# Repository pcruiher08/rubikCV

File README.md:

# rubikCV

## Objectives

## Approach

## Development

### Mechanics
#### Brief discussion about motors
#### MoYu Weilong gts v2
#### First design (unreliable)
#### Second design (screenshots and video)
#### Screw joint design
#### Motor-Cube joints
#### 3D printing and laser cutting

### Electronics
#### Controller decision (raspberry)
#### A4988 Motor driver
#### LCD
#### 18650 lithium batteries
#### LEDs
#### Arduino with LEDs and how it would be implemented on the raspberry (level shifter)
#### Brief disccussion about the pcb and the breadboard
#### WebCam

### Software

#### OpenCV justification
* Image processing (5 pictures per face)
* Arucos (Augmented reality and geometry functions)
* HSV
* Dominant Color algorithm
#### Cube map (diagrams, polygon class)
#### States machine (scanning phase with pre defined movements)
#### Kociemba
#### Motor movement (parser, motor class, motor speed)
#### LEDs
#### LCD (LCD class)

## Results

## Improvements

## Conlusions

## DIY

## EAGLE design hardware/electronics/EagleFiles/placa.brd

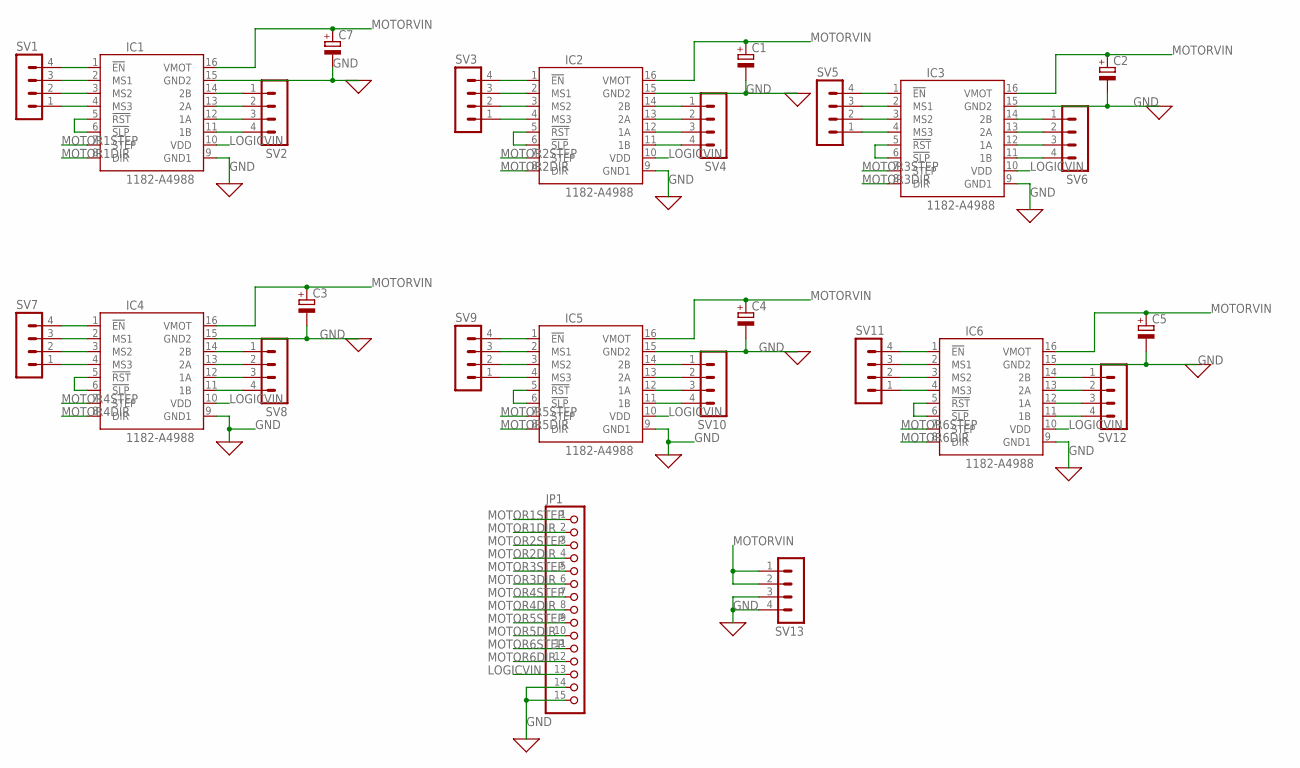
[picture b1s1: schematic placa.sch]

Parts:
C1, C2, C3, C4, C5, C7: CPOL-EUE2.5-7; E2,5-7
IC1, IC2, IC3, IC4, IC5, IC6: 1182-A4988; A4988
JP1: PINHD-1X15; 1X15
SV1, SV2, SV3, SV4, SV5, SV6, SV7, SV8, SV9, SV10, SV11, SV12, SV13: MA04-1

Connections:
GND: C1.-, C2.-, C3.-, C4.-, C5.-, C7.-, IC1.9 (GND1), IC1.15 (GND2), IC2.9 (GND1), IC2.15 (GND2), IC3.9 (GND1), IC3.15 (GND2), IC4.9 (GND1), IC4.15 (GND2), IC5.9 (GND1), IC5.15 (GND2), IC6.9 (GND1), IC6.15 (GND2), JP1.14, JP1.15, SV13.3, SV13.4
LOGICVIN: IC1.10 (VDD), IC2.10 (VDD), IC3.10 (VDD), IC4.10 (VDD), IC5.10 (VDD), IC6.10 (VDD), JP1.13
MOTOR1DIR: IC1.8 (DIR), JP1.2
MOTOR1STEP: IC1.7 (STEP), JP1.1
MOTOR2DIR: IC2.8 (DIR), JP1.4
MOTOR2STEP: IC2.7 (STEP), JP1.3
MOTOR3DIR: IC3.8 (DIR), JP1.6
MOTOR3STEP: IC3.7 (STEP), JP1.5
MOTOR4DIR: IC4.8 (DIR), JP1.8
MOTOR4STEP: IC4.7 (STEP), JP1.7
MOTOR5DIR: IC5.8 (DIR), JP1.10
MOTOR5STEP: IC5.7 (STEP), JP1.9
MOTOR6DIR: IC6.8 (DIR), JP1.12
MOTOR6STEP: IC6.7 (STEP), JP1.11
MOTORVIN: C1.+, C2.+, C3.+, C4.+, C5.+, C7.+, IC1.16 (VMOT), IC2.16 (VMOT), IC3.16 (VMOT), IC4.16 (VMOT), IC5.16 (VMOT), IC6.16 (VMOT), SV13.1, SV13.2
unnamed: IC1.1 (!EN), SV1.4
unnamed: IC1.2 (MS1), SV1.3
unnamed: IC1.3 (MS2), SV1.2
unnamed: IC1.4 (MS3), SV1.1
unnamed: IC1.5 (!RST), IC1.6 (!SLP)
unnamed: IC2.1 (!EN), SV3.4
unnamed: IC2.2 (MS1), SV3.3
unnamed: IC2.3 (MS2), SV3.2
unnamed: IC1.14 (2B), SV2.1
unnamed: IC1.13 (2A), SV2.2
unnamed: IC1.12 (1A), SV2.3
unnamed: IC1.11 (1B), SV2.4
unnamed: IC2.4 (MS3), SV3.1
unnamed: IC2.5 (!RST), IC2.6 (!SLP)
unnamed: IC2.14 (2B), SV4.1
unnamed: IC2.13 (2A), SV4.2
unnamed: IC2.12 (1A), SV4.3
unnamed: IC2.11 (1B), SV4.4
unnamed: IC3.1 (!EN), SV5.4
unnamed: IC3.2 (MS1), SV5.3
unnamed: IC3.3 (MS2), SV5.2
unnamed: IC3.4 (MS3), SV5.1
unnamed: IC3.5 (!RST), IC3.6 (!SLP)
unnamed: IC3.14 (2B), SV6.1
unnamed: IC3.13 (2A), SV6.2
unnamed: IC3.12 (1A), SV6.3
unnamed: IC3.11 (1B), SV6.4
unnamed: IC4.1 (!EN), SV7.4
unnamed: IC4.2 (MS1), SV7.3
unnamed: IC4.3 (MS2), SV7.2
unnamed: IC4.4 (MS3), SV7.1
unnamed: IC4.5 (!RST), IC4.6 (!SLP)
unnamed: IC4.14 (2B), SV8.1
unnamed: IC4.13 (2A), SV8.2
unnamed: IC4.12 (1A), SV8.3
unnamed: IC4.11 (1B), SV8.4
unnamed: IC5.1 (!EN), SV9.4
unnamed: IC5.2 (MS1), SV9.3
unnamed: IC5.3 (MS2), SV9.2
unnamed: IC5.4 (MS3), SV9.1
unnamed: IC5.5 (!RST), IC5.6 (!SLP)
unnamed: IC5.14 (2B), SV10.1
unnamed: IC5.13 (2A), SV10.2
unnamed: IC5.12 (1A), SV10.3
unnamed: IC5.11 (1B), SV10.4
unnamed: IC6.1 (!EN), SV11.4
unnamed: IC6.2 (MS1), SV11.3
unnamed: IC6.3 (MS2), SV11.2
unnamed: IC6.4 (MS3), SV11.1
unnamed: IC6.5 (!RST), IC6.6 (!SLP)
unnamed: IC6.14 (2B), SV12.1
unnamed: IC6.13 (2A), SV12.2
unnamed: IC6.12 (1A), SV12.3
unnamed: IC6.11 (1B), SV12.4

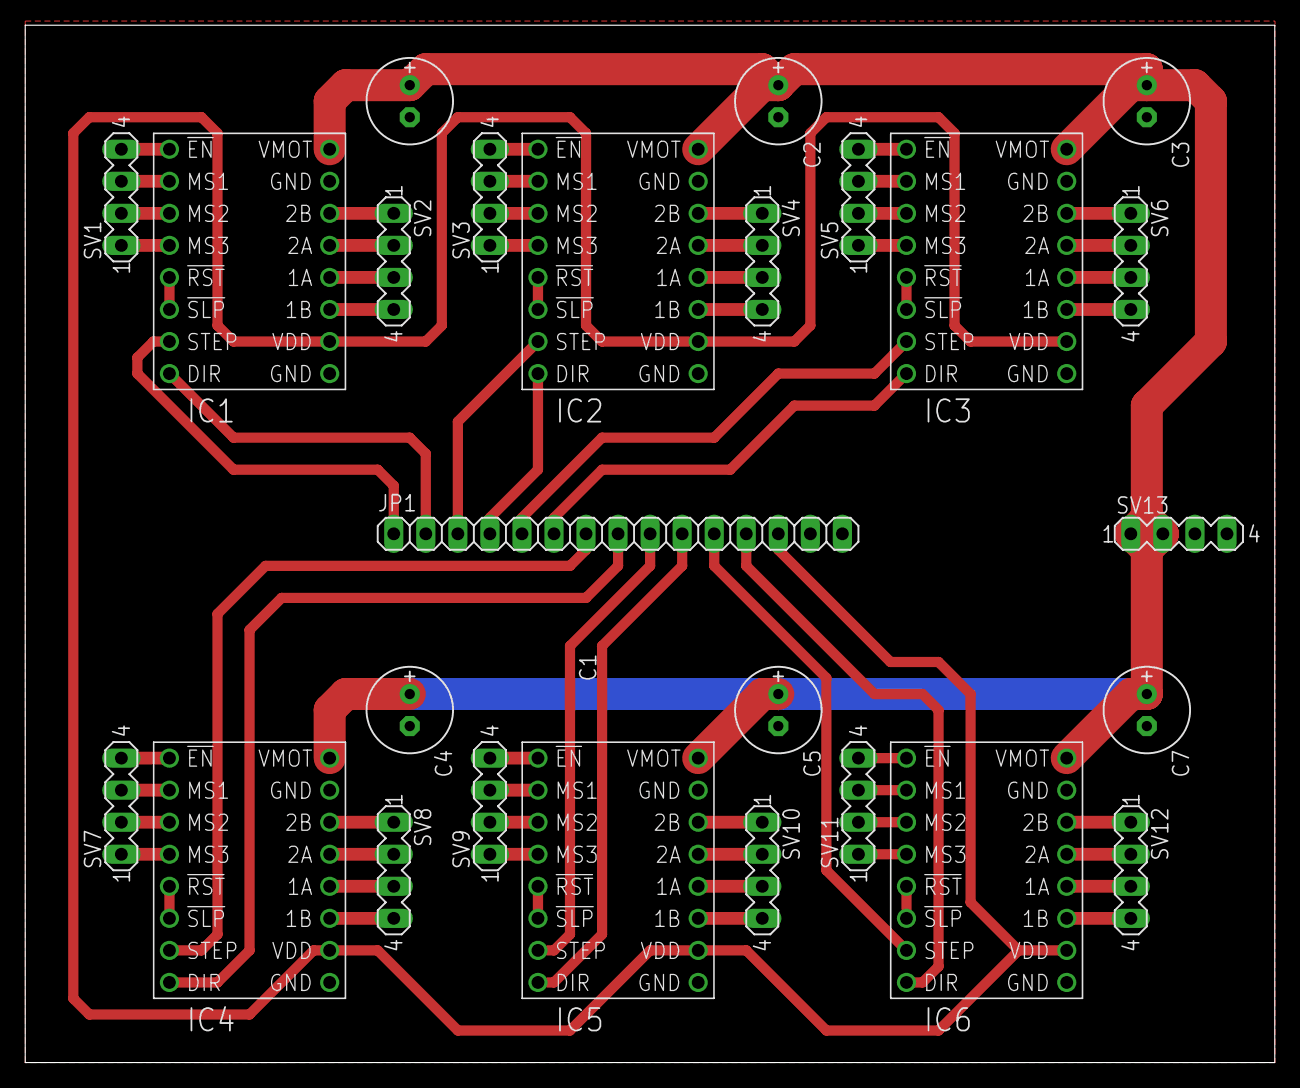
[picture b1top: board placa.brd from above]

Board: 2 copper layers, 99.0 x 82.2 mm, 26 parts (0 on the bottom side), 69 nets.

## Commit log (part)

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2021-05-28 faster
2021-05-28 back motor]
2021-05-28 one motor
2021-05-28 second motor test
2021-05-28 two at once
2021-05-28 olasod
2021-05-28 lipo
2021-05-28 back
2021-05-28 six motors
2021-05-28 turn delay
2021-05-28 duerme
2021-05-28 tests
2021-05-28 auayayay
2021-05-28 si esto no jala, estoy en problemas
2021-05-28 si esto no jala, estoy en problemas x2
2021-05-28 porfis
2021-05-28 otro test
2021-05-28 speeeed
2021-05-28 speeeeeed
2021-05-29 foto del chuerk
2021-05-29 todo estaba volteado aaaaaaaa
2021-05-29 a ver si es cierto
2021-05-29 por favor
2021-05-29 arucos
2021-05-29 aruco pictures
2021-05-29 un patron
2021-05-29 six centers
2021-05-29 scan
2021-05-29 sleep
2021-05-29 wake up
2021-05-29 side correction in scanning phase
2021-05-29 circulo?
2021-05-29 linea
2021-05-29 linea?
2021-05-29 lineas?
2021-05-29 punto
2021-05-30 blanco?
2021-05-30 foto
2021-05-31 led test
2021-05-31 leds
2021-06-01 test con leds
2021-06-02 poligono c1
2021-06-02 overlay test
2021-06-02 polygon class
2021-06-02 aaaa
2021-06-02 otra foto
2021-06-02 ahi va otra
2021-06-02 otra?
2021-06-02 colorcuadrant better version
2021-06-02 centroid calculation of a polygon
2021-06-02 colorbetter
2021-06-02 con video ya segmentado
2021-06-02 red abajo de orange en prioridad
2021-06-02 test deteccion en funcion
2021-06-03 segun Humberto, va a correr
2021-06-03 Humberto tenia razon
2021-06-03 contours special
2021-06-03 5 fotos
2021-06-03 5 fotos con colores
2021-06-03 foto to img
2021-06-03 sin foto
2021-06-03 ciclo 5
2021-06-03 ciclo 5 fix
2021-06-03 aruco processing
2021-06-03 motores
2021-06-03 motores con fotos test
2021-06-03 ya casi acabamos
2021-06-03 done before testing
2021-06-03 printing colors
2021-06-03 color map fix
2021-06-03 string parser and cube printing
2021-06-03 imprimir matrices
2021-06-03 matrix print fix
2021-06-03 corregir secuencia
2021-06-03 done
2021-06-03 orange new hsv value
2021-06-03 fotos de estados
2021-06-03 guarda
2021-06-03 guarda las fotos
2021-06-03 guarda las fotos con jpg
2021-06-03 fotos
2021-06-03 test naranja hsv
2021-06-03 fix green face
2021-06-03 green fix ahora si
2021-06-03 mas pixeles para detectar
2021-06-03 new orange hsv
2021-06-03 fotos nuevas
2021-06-03 blue fix
2021-06-03 es jugada riesgosa eso del rojo pero asi correlo -Humberto
2021-06-03 rojo a 8 de nuevo
2021-06-03 un punto en la maskara
2021-06-04 demostracion
2021-06-04 kociembracode
2021-06-04 kociembracode correcto por favor funciona pls pls pls pls pls pls plssssssssssssssss
2021-06-04 over optimistic?
2021-06-04 scramble
2021-06-04 mas lento
2021-06-04 unverto quiere que este maaaas lento
2021-06-04 quick cleanup
2021-06-04 more cleanup
2021-06-04 leds?
2021-06-06 reordenar
2021-06-06 readme update esqueleto
2021-06-06 headers
2021-06-06 bullets
2021-06-06 line break
2021-06-07 readme updates
